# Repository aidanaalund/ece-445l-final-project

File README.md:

# ECE 445L Final Project

This final project is titled 'Magic Wand'. The user's hand is tracked with a sensor and the fans in the tubes will make a ping pong ball float to match the user's hand distance. Won professor's vote at the Spring 2025 Embedded Systems competition.

## 0 Repository Structure

The typical explanation for the repo structure. Lab specific instructions can be
found further below.

### 0.1 HW

The `hw` folder should contain your schematic and board files for your PCB or
circuits. In labs 1-5 and 10, you will be creating schematics for your circuit
in KiCad. 

### 0.2 SW

The `sw` folder should contain your application firmware and software written
for the lab. The `sw/inc` folder contains firmware drivers written for you by
Professor Valvano. Feel free to write your own (in fact, in some labs, you may
be required to write your own).

You can place any other source files in the `sw` folder. TAs will look at the
files you create and/or modify for software quality and for running your
project.

### 0.3 Resources

A couple files are provided in the Resources folder so you don't have to keep
searching for that one TI document. Some of them are immediately useful, like
the TM4C datasheet. Others may be useful for your final project, like the
TM4C_System_Design_Guidelines page.

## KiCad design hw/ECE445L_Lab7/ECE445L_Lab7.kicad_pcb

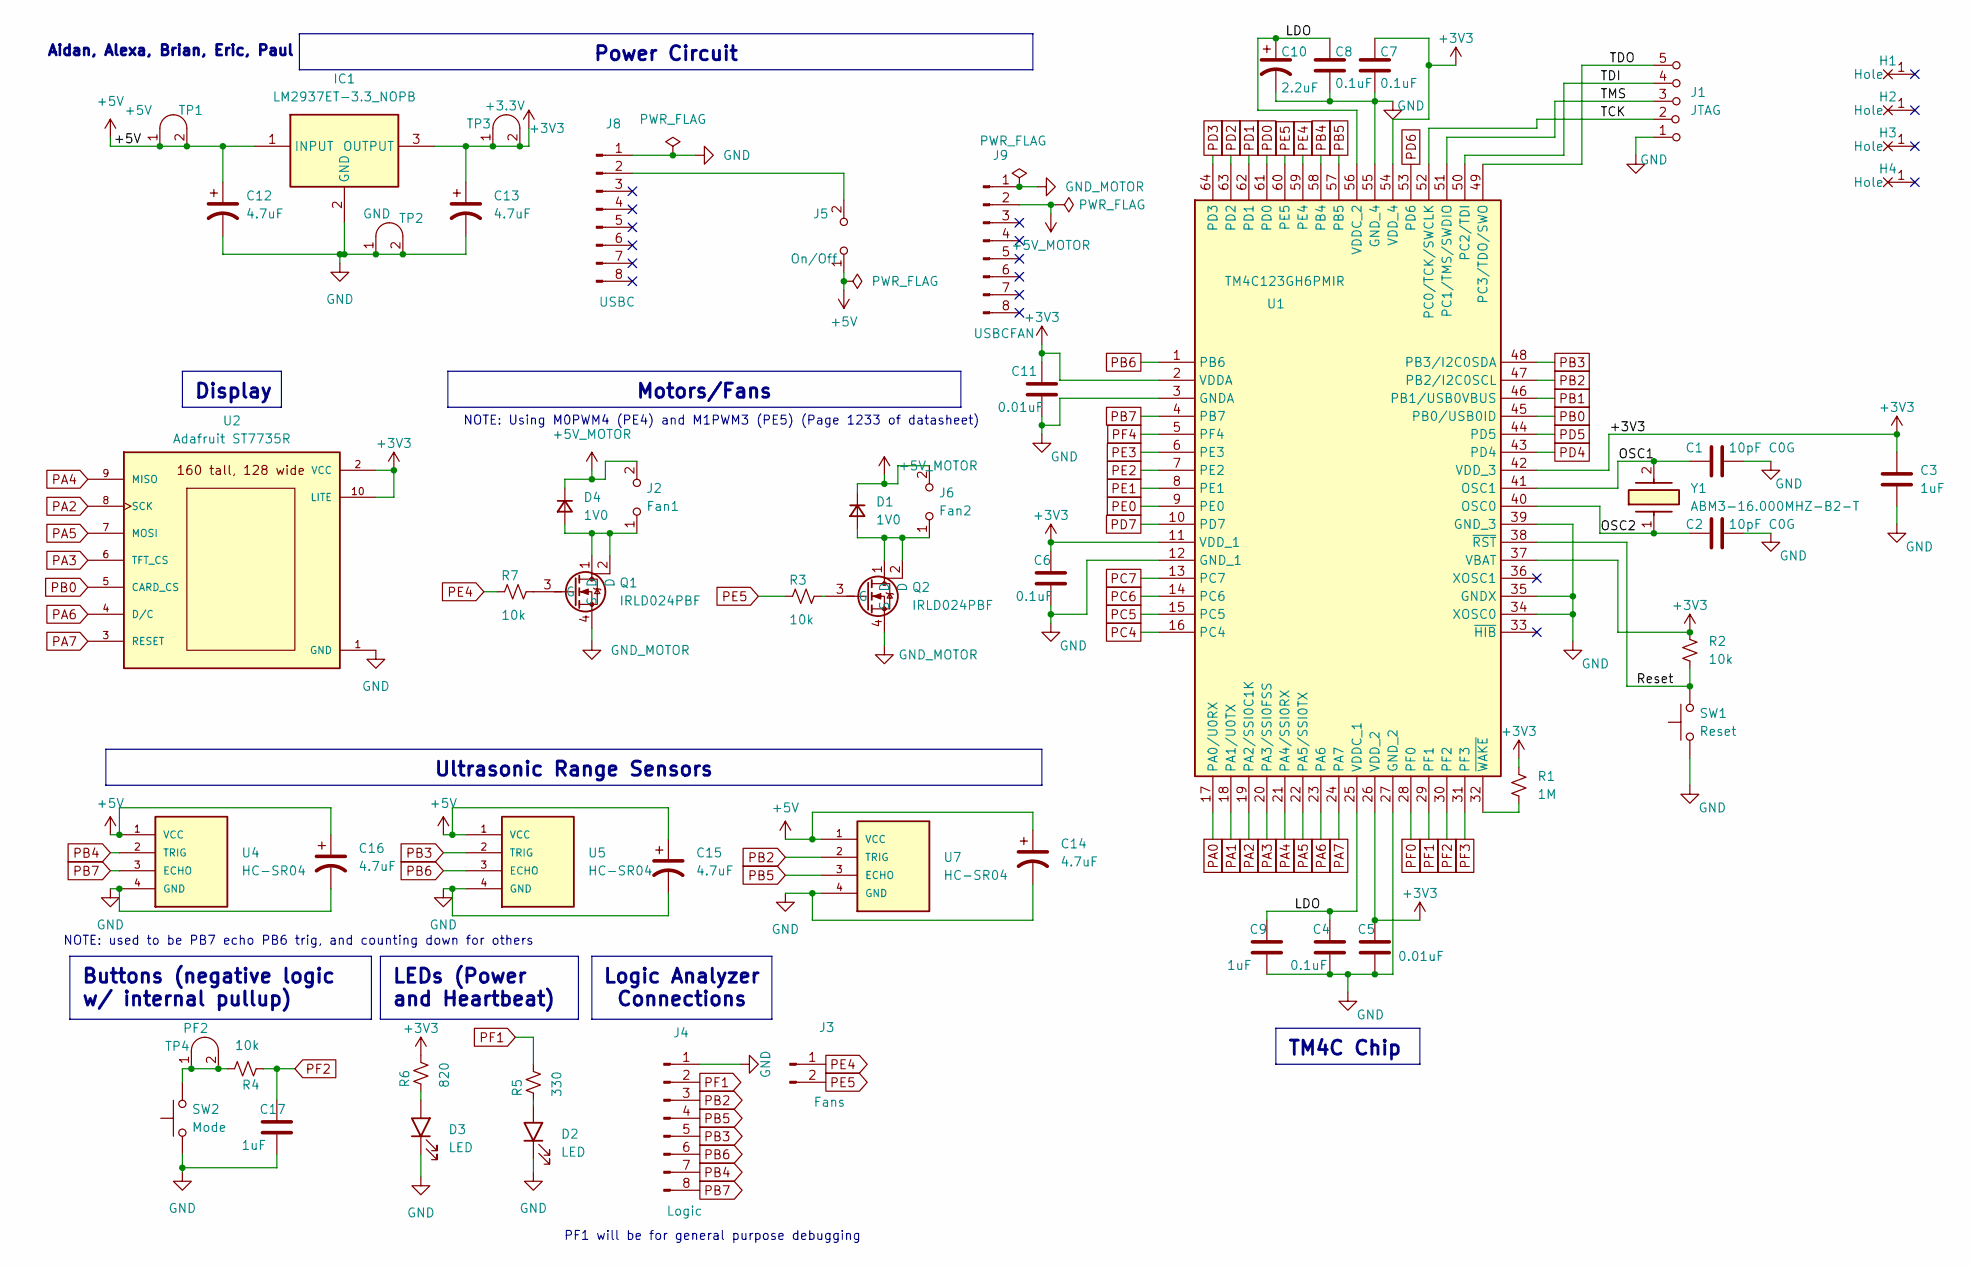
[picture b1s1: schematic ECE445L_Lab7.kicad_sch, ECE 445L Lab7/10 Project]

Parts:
C1, C2: 10pF C0G; C_Axial_200mil
C3, C9, C17: 1uF; C_Axial_200mil
C4, C6, C7, C8: 0.1uF; C_Axial_200mil
C5, C11: 0.01uF; C_Axial_200mil
C10: 2.2uF; CP_Radial_Tantal200mil
C12, C13, C14, C15, C16: 4.7uF; CP_Radial_Tantal200mil
D1, D4: 1V0; AFL-W2C8.9D
D2, D3: LED; LED_D5.0mm
H1, H2, H3, H4: MountingHole_4_40
IC1: LM2937ET-3.3_NOPB; TO254P470X1028X1955-3P; Mouser Part Number 926-LM2937ET-3.3NOPB
J1: JTAG; PinHeader_1x05_P2.54mm_Vertical
J2: Fan1; PinHeader_1x02_P2.54mm_Vertical
J3: Fans; PinHeader_1x02_P2.54mm_Vertical
J4: Logic; PinHeader_1x08_P2.54mm_Vertical
J5: On/Off; PinHeader_1x02_P2.54mm_Vertical
J6: Fan2; PinHeader_1x02_P2.54mm_Vertical
J8: USBC; PinHeader_1x08_P2.54mm_Vertical
J9: USBCFAN; PinHeader_1x08_P2.54mm_Vertical
Q1, Q2: IRLD024PBF; DIP920W60P254L490H457Q4N; Mouser Part Number 844-IRLD024PBF
R1: 1M; R_Axial_DIN0204_L3.6mm_D1.6mm_P7.62mm_Horizontal
R2, R3, R4, R7: 10k; R_Axial_DIN0204_L3.6mm_D1.6mm_P7.62mm_Horizontal
R5: 330; R_Axial_DIN0204_L3.6mm_D1.6mm_P7.62mm_Horizontal
R6: 820; R_Axial_DIN0204_L3.6mm_D1.6mm_P7.62mm_Horizontal
SW1: Reset; SW_PUSH_6mm
SW2: Mode; SW_PUSH_6mm
TP1: +5V; Testpoint_1x02_P2.54mm
TP2: GND; Testpoint_1x02_P2.54mm
TP3: +3.3V; Testpoint_1x02_P2.54mm
TP4: PF2; Testpoint_1x02_P2.54mm
U1: TM4C123GH6PMIR; QFP50P1200X1200X160-64N; Mouser Part Number 595-TM4C123GH6PMIR
U2: Adafruit ST7735R; adafruit_st7735r2
U4, U5, U7: HC-SR04; PinHeader_1x04_P2.54mm_Vertical
Y1: ABM3-16.000MHZ-B2-T; ABM3; Mouser Part Number 815-ABM3-16-B2-T

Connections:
+3V3: C3.1, C5.1, C6.1, C7.1, C11.1, C13.1, IC1.3 (OUTPUT), R1.1, R2.1, R6.2, TP3.1 (A), TP3.2 (B), U1.2 (VDDA), U1.11 (VDD_1), U1.26 (VDD_2), U1.37 (VBAT), U1.42 (VDD_3), U1.54 (VDD_4), U2.2 (VCC), U2.10 (LITE)
+5V: C12.1, C14.1, C15.1, C16.1, IC1.1 (INPUT), J5.1 (A), TP1.1 (A), TP1.2 (B), U4.1 (VCC), U5.1 (VCC), U7.1 (VCC)
+5V_MOTOR: D1.1 (K), D4.1 (K), J2.2 (B), J6.2 (B), J9.2
/LDO: C4.1, C8.1, C9.1, C10.1, U1.25 (VDDC_1), U1.56 (VDDC_2)
/OSC1: C1.1, U1.41 (OSC1), Y1.2
/OSC2: C2.1, U1.40 (OSC0), Y1.1
/Reset: R2.2, SW1.2, U1.38 (~RST)
/TCK: J1.2 (B), U1.52 (PC0/TCK/SWCLK)
/TDI: J1.4 (C), U1.50 (PC2/TDI)
/TDO: J1.5 (C), U1.49 (PC3/TDO/SWO)
/TMS: J1.3 (C), U1.51 (PC1/TMS/SWDIO)
GND: C1.2, C2.2, C3.2, C4.2, C5.2, C6.2, C7.2, C8.2, C9.2, C10.2, C11.2, C12.2, C13.2, C14.2, C15.2, C16.2, C17.2, D2.1 (K), D3.1 (K), IC1.2 (GND), J1.1 (A), J4.1, J8.1, SW1.1, SW2.1, TP2.1 (A), TP2.2 (B), U1.3 (GNDA), U1.12 (GND_1), U1.27 (GND_2), U1.34 (XOSC0), U1.35 (GNDX), U1.39 (GND_3), U1.55 (GND_4), U2.1 (GND), U4.4 (GND), U5.4 (GND), U7.4 (GND)
GND_MOTOR: J9.1, Q1.4 (S), Q2.4 (S)
unnamed: D1.2 (A), J6.1 (A), Q2.1 (D), Q2.2 (D)
unnamed: D2.2 (A), R5.1
unnamed: D3.2 (A), R6.1
unnamed: D4.2 (A), J2.1 (A), Q1.1 (D), Q1.2 (D)
unnamed: J5.2 (B), J8.2
unnamed: Q1.3 (G), R7.2
unnamed: Q2.3 (G), R3.2
unnamed: R4.2, SW2.2, TP4.1 (A), TP4.2 (B)
unnamed: R1.2, U1.32 (~WAKE)
PA0: U1.17 (PA0/U0RX)
PA1: U1.18 (PA1/U0TX)
PA2: U1.19 (PA2/SSI0C1K), U2.8 (SCK)
PA3: U1.20 (PA3/SSI0FSS), U2.6 (TFT_CS)
PA4: U1.21 (PA4/SSI0RX), U2.9 (MISO)
PA5: U1.22 (PA5/SSI0TX), U2.7 (MOSI)
PA6: U1.23 (PA6), U2.4 (D/C)
PA7: U1.24 (PA7), U2.3 (RESET)
PB0: U1.45 (PB0/USB0ID), U2.5 (CARD_CS)
PB1: U1.46 (PB1/USB0VBUS)
PB2: J4.3, U1.47 (PB2/I2C0SCL), U7.2 (TRIG)
PB3: J4.5, U1.48 (PB3/I2C0SDA), U5.2 (TRIG)
PB4: J4.7, U1.58 (PB4), U4.2 (TRIG)
PB5: J4.4, U1.57 (PB5), U7.3 (ECHO)
PB6: J4.6, U1.1 (PB6), U5.3 (ECHO)
PB7: J4.8, U1.4 (PB7), U4.3 (ECHO)
PC4: U1.16 (PC4)
PC5: U1.15 (PC5)
PC6: U1.14 (PC6)
PC7: U1.13 (PC7)
PD0: U1.61 (PD0)
PD1: U1.62 (PD1)
PD2: U1.63 (PD2)
PD3: U1.64 (PD3)
PD4: U1.43 (PD4)
PD5: U1.44 (PD5)
PD6: U1.53 (PD6)
PD7: U1.10 (PD7)
PE0: U1.9 (PE0)
PE1: U1.8 (PE1)
PE2: U1.7 (PE2)
PE3: U1.6 (PE3)
PE4: J3.1, R7.1, U1.59 (PE4)
PE5: J3.2, R3.1, U1.60 (PE5)
PF0: U1.28 (PF0)
PF1: J4.2, R5.2, U1.29 (PF1)
PF2: C17.1, R4.1, U1.30 (PF2)
PF3: U1.31 (PF3)
PF4: U1.5 (PF4)

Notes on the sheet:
Logic Analyzer Connections
Buttons (negative logic w/ internal pullup)
Motors/Fans
LEDs (Power and Heartbeat)
Ultrasonic Range Sensors
Display
Power Circuit
TM4C Chip
NOTE: used to be PB7 echo PB6 trig, and counting down for others
PF1 will be for general purpose debugging
Aidan, Alexa, Brian, Eric, Paul
NOTE: Using M0PWM4 (PE4) and M1PWM3 (PE5) (Page 1233 of datasheet)

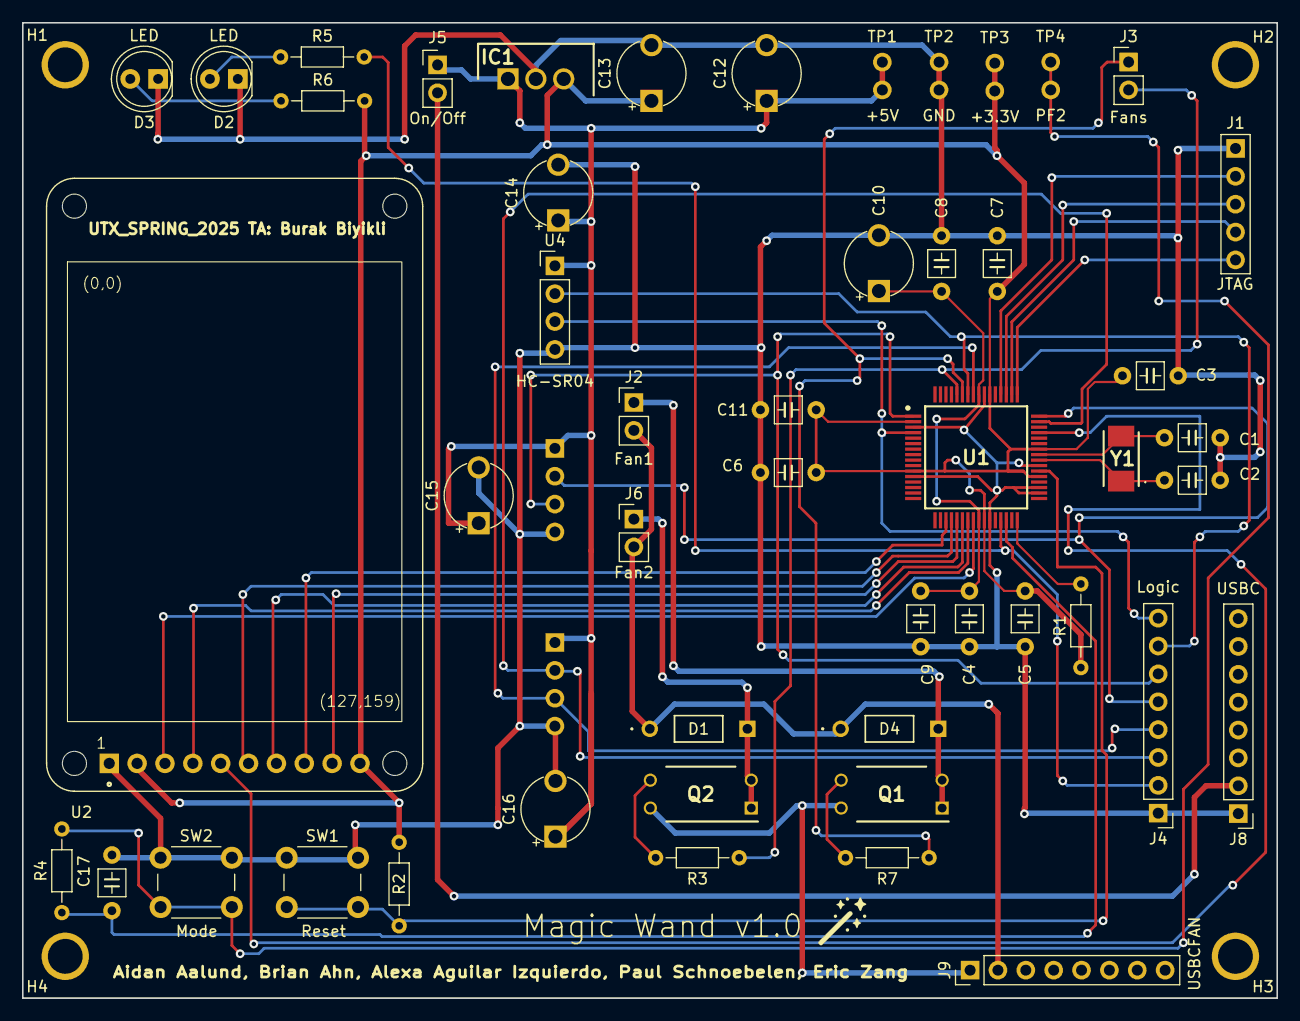
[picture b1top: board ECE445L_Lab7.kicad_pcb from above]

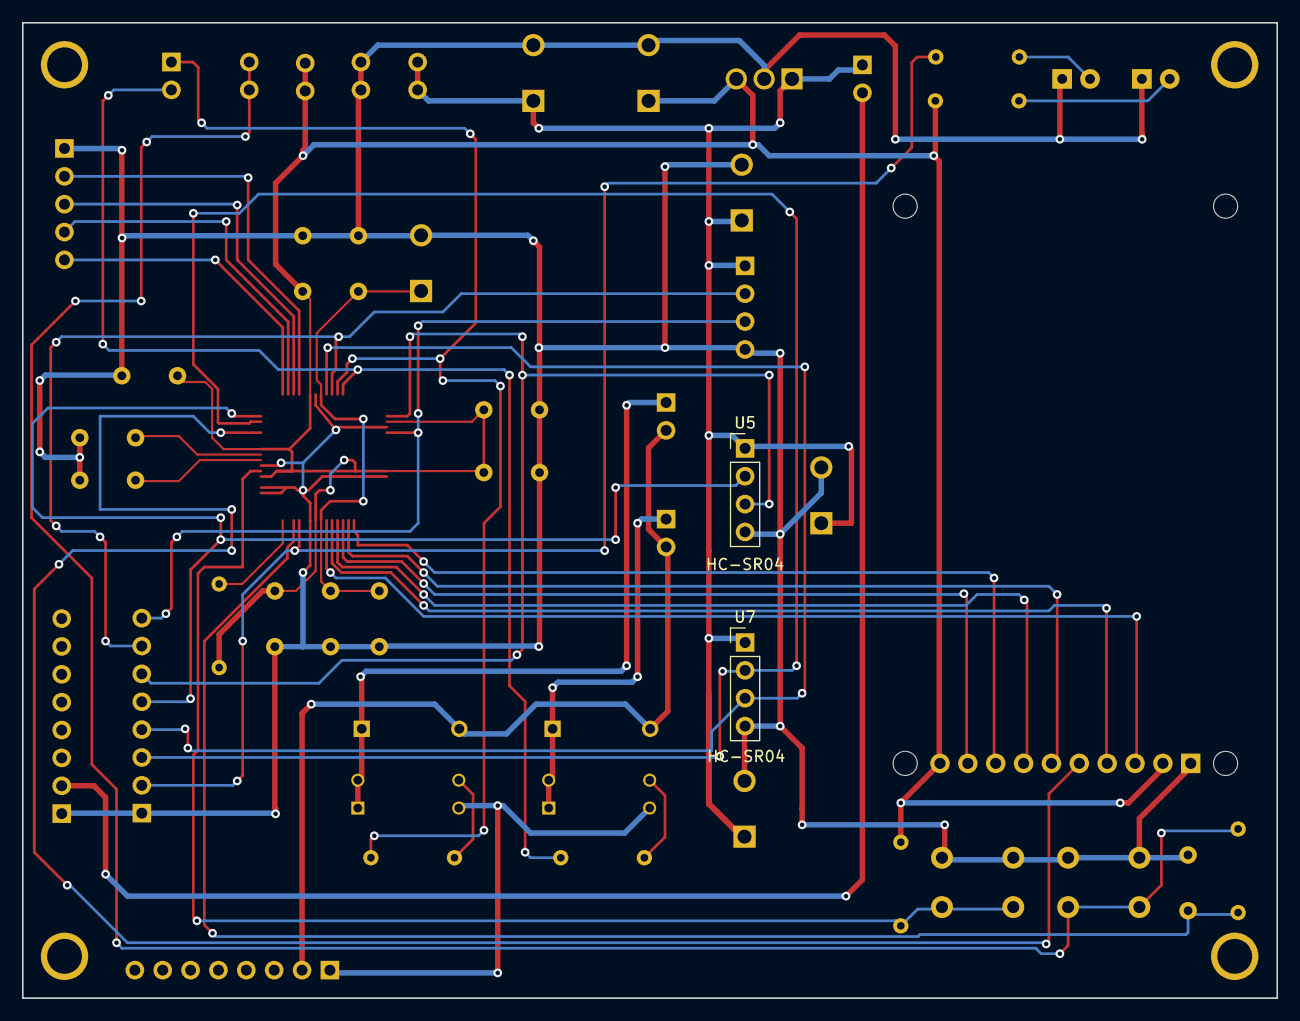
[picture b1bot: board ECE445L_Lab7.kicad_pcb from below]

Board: 2 copper layers, 114.4 x 88.9 mm, 55 parts (2 on the bottom side), 39 nets.

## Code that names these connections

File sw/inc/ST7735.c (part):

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// ST7735
// Backlight (pin 10) connected to +3.3 V
// MISO (pin 9) unconnected
// SCK (pin 8) connected to PA2 (SSI0Clk)
// MOSI (pin 7) connected to PA5 (SSI0Tx)
// TFT_CS (pin 6) connected to PA3 (SSI0Fss)
// CARD_CS (pin 5) unconnected
// Data/Command (pin 4) connected to PA6 (GPIO), high for data, low for command
// RESET (pin 3) connected to PA7 (GPIO)
// VCC (pin 2) connected to +3.3 V
// Gnd (pin 1) connected to ground

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// Silkscreen Label (SDC side up; LCD side down) - Connection
// VCC  - +3.3 V
// GND  - Ground
// !SCL - PA2 Sclk SPI clock from microcontroller to TFT or SDC
// !SDA - PA5 MOSI SPI data from microcontroller to TFT or SDC
// DC   - PA6 TFT data/command
// RES  - PA7 TFT reset
// CS   - PA3 TFT_CS, active low to enable TFT
// *CS  - (NC) SDC_CS, active low to enable SDC
// MISO - (NC) MISO SPI data from SDC to microcontroller
// SDA   (NC) I2C data for ADXL345 accelerometer
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// Silkscreen Label (SDC side up; LCD side down) - Connection
// VCC  - +3.3 V
// GND  - Ground
// !SCL - PA2 Sclk SPI clock from microcontroller to TFT or SDC
// !SDA - PA5 MOSI SPI data from microcontroller to TFT or SDC
// DC   - PA6 TFT data/command
// RES  - PA7 TFT reset
// CS   - PA3 TFT_CS, active low to enable TFT
// *CS  - (NC) SDC_CS, active low to enable SDC
// MISO - (NC) MISO SPI data from SDC to microcontroller
// X (NC) analog input X-axis from ADXL335 accelerometer
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// MOSI   (pin 13) SDC, MOSI
// MISO   (pin 12) SDC, MISO
// SCK    (pin 11) SDC, serial clock
// CS     (pin 10) TFT, PA3 (SSI0Fss)
// SCL    (pin 9)  TFT, SCK  PA2 (SSI0Clk)
// SDA    (pin 8)  TFT, MOSI PA5 (SSI0Tx)
// A0     (pin 7)  TFT, Data/Command PA6 (GPIO), high for data, low for command
// RESET  (pin 6)  TFT, to PA7 (GPIO)
// NC     (pins 3,4,5) not connected
// VCC    (pin 2)  connected to +3.3 V
// GND    (pin 1)  connected to ground
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// Tyenaza Tyenazaqhf72mi9s3
// ST7735
// LED (pin 8) connected to +3.3 V
// SCK (pin 7) connected to PA2 (SSI0Clk)
// SDA (pin 6) MOSI, connected to PA5 (SSI0Tx)
// A0  (pin 5) Data/Command connected to PA6 (GPIO), high for data, low for command
// RESET (pin 4) connected to PA7 (GPIO)
// CS  (pin 3) connected to PA3 (SSI0Fss)
// Gnd (pin 2) connected to ground
// VCC (pin 1) connected to +3.3 V

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
  // toggle RST low to reset; CS low so it'll listen to us
  // SSI0Fss is temporarily used as GPIO
  GPIO_PORTA_DIR_R |= 0xC8;             // make PA3,6,7 out
  GPIO_PORTA_AFSEL_R &= ~0xC8;          // disable alt funct on PA3,6,7
  GPIO_PORTA_DEN_R |= 0xC8;             // enable digital I/O on PA3,6,7
                                        // configure PA3,6,7 as GPIO
  GPIO_PORTA_PCTL_R = (GPIO_PORTA_PCTL_R&0x00FF0FFF)+0x00000000;
  GPIO_PORTA_AMSEL_R &= ~0xC8;          // disable analog functionality on PA3,6,7
  TFT_CS = TFT_CS_LOW;
  RESET = RESET_HIGH;
  Delay1ms(500);
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  Delay1ms(500);

  // initialize SSI0
  GPIO_PORTA_AFSEL_R |= 0x2C;           // enable alt funct on PA2,3,5
  GPIO_PORTA_DEN_R |= 0x2C;             // enable digital I/O on PA2,3,5
                                        // configure PA2,3,5 as SSI
  GPIO_PORTA_PCTL_R = (GPIO_PORTA_PCTL_R&0xFF0F00FF)+0x00202200;
  GPIO_PORTA_AMSEL_R &= ~0x2C;          // disable analog functionality on PA2,3,5
  SSI0_CR1_R &= ~SSI_CR1_SSE;           // disable SSI
  SSI0_CR1_R &= ~SSI_CR1_MS;            // master mode
                                        // configure for system clock/PLL baud clock source
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
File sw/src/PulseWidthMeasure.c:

// PulseWidthMeasure.c
// Runs on LM4F120/TM4C123
// Use Timer0A in 24-bit edge time mode to request interrupts on the falling
// edge of PB6 (T0CCP0). 
// Use Timer0B in 24-bit edge time mode rising edge of PB7(T0CCP1) is latched, and 
// the system measures pulse between pulses.
// Daniel Valvano
// April 2, 2018

/* This example accompanies the book
   "Embedded Systems: Real Time Interfacing to Arm Cortex M Microcontrollers",
   ISBN: 978-1463590154, Jonathan Valvano, copyright (c) 2018
   Example 6.5, Program 6.5

 Copyright 2018 by Jonathan W. Valvano, valvano@mail.utexas.edu
    You may use, edit, run or distribute this file
    as long as the above copyright notice remains
 THIS SOFTWARE IS PROVIDED "AS IS".  NO WARRANTIES, WHETHER EXPRESS, IMPLIED
 OR STATUTORY, INCLUDING, BUT NOT LIMITED TO, IMPLIED WARRANTIES OF
 MERCHANTABILITY AND FITNESS FOR A PARTICULAR PURPOSE APPLY TO THIS SOFTWARE.
 VALVANO SHALL NOT, IN ANY CIRCUMSTANCES, BE LIABLE FOR SPECIAL, INCIDENTAL,
 OR CONSEQUENTIAL DAMAGES, FOR ANY REASON WHATSOEVER.
 For more information about my classes, my research, and my books, see
 http://users.ece.utexas.edu/~valvano/
 */


#include <stdint.h>
#include "PulseWidthMeasure.h"
#include "Motor.h"
#include "../inc/Timer0A.h"
#include "../inc/Timer2A.h" // USE THESE TWO WHEN YOU INTEGRATE
#include "../inc/Timer3A.h" // ................................
#include "../inc/tm4c123gh6pm.h"
#include "../inc/PLL.h"
#include "../inc/CortexM.h"
#include "../inc/LaunchPad.h"

uint32_t startTimeTubeOne = 0;
uint32_t startTimeTubeTwo = 0;
uint32_t startTimeTubeThree = 0;

volatile uint32_t distanceOne = 0;
volatile uint32_t distanceTwo = 0;
volatile uint32_t distanceThree = 0;

volatile uint32_t Count = 0;
volatile uint32_t Count2 = 0;

uint32_t firstClock = 0;

int tubeDoneOne = 0;                   // set each falling
int tubeDoneTwo = 0;
int tubeDoneThree = 0;

//void timeInMicro (void) {
//	Count += 1;
//}

void Timer2PWMMeasure_Init(void) {
    // Enable the clock for Timer 2
    SYSCTL_RCGCTIMER_R |= SYSCTL_RCGCTIMER_R2;  
    while ((SYSCTL_PRTIMER_R & SYSCTL_PRTIMER_R2) == 0);  // Wait for Timer 2 to be ready

    // Disable Timer 2 before configuration
    TIMER2_CTL_R = 0;

    // Configure Timer 2 as a 32-bit timer
    TIMER2_CFG_R = TIMER_CFG_32_BIT_TIMER;

    // Set Timer 2 to periodic mode
    TIMER2_TAMR_R = TIMER_TAMR_TAMR_PERIOD;  // Periodic mode

    // Set the direction to count up (clear TACDIR for up-counting)
    TIMER2_TAMR_R &= ~TIMER_TAMR_TACDIR;  // Clear the TACDIR bit to make it count up

    // Set the maximum value for the timer (maximum 32-bit value)
    TIMER2_TAILR_R = 0xFFFFFFFF;  // Set to maximum 32-bit value (up to 4,294,967,295)

    // Enable Timer 2A
    TIMER2_CTL_R |= TIMER_CTL_TAEN;
}

void GPIOPortB_Handler(void){
	
	if (GPIO_PORTB_RIS_R & 0x80) {// pb7
		GPIO_PORTB_ICR_R = 0x80;
		if (tubeDoneOne == 0) {
			tubeDoneOne = 1;
			startTimeTubeOne = TIMER2_TAR_R;
			GPIO_PORTB_DATA_R |= 0x02;
		} else if (tubeDoneOne == 1) {
			GPIO_PORTB_DATA_R &= ~0x02;
			if (TIMER2_TAR_R < startTimeTubeOne) { 
				uint32_t test = TIMER2_TAR_R;
				distanceOne = startTimeTubeOne - TIMER2_TAR_R; /// 29; // Fixed point (units of 0.5cm) (moved to display.c)
			} else {
				uint32_t test = TIMER2_TAR_R;
				distanceOne = (startTimeTubeOne + 0xFFFFFFFF)- TIMER2_TAR_R ; // MIGHT NEED TO MAKE THIS VOLATILE
			}
			//if(distanceOne > 100){distanceOne = 0;} // 50cm cap
			tubeDoneOne = 0;
		}

	}
	
	if (GPIO_PORTB_RIS_R & 0x40) {// pb6
		GPIO_PORTB_ICR_R = 0x40;
		uint32_t test = TIMER2_TAR_R;
		if (tubeDoneTwo == 0) {
			tubeDoneTwo = 1;
			startTimeTubeTwo = TIMER2_TAR_R;
		} else if (tubeDoneTwo == 1) {
			if (TIMER2_TAR_R < startTimeTubeTwo) { 
				distanceTwo =  startTimeTubeTwo - TIMER2_TAR_R; /// 29; // Fixed point (units of 0.5cm) (moved to display.c)
			} else {
				distanceTwo = (startTimeTubeTwo + 0xFFFFFFFF)- TIMER2_TAR_R; // MIGHT NEED TO MAKE THIS VOLATILE
			}
			tubeDoneTwo = 0;
		}

	}
	
	if (GPIO_PORTB_RIS_R & 0x20) {// pb5
		GPIO_PORTB_ICR_R = 0x20;
		if (tubeDoneThree == 0) {
			tubeDoneThree = 1;
			startTimeTubeThree = TIMER2_TAR_R;
		} else if (tubeDoneThree == 1) {
			if (TIMER2_TAR_R < startTimeTubeThree) { 
				distanceThree = startTimeTubeThree - TIMER2_TAR_R; /// 29; // Fixed point (units of 0.5cm) (moved to display.c)
			} else {
				distanceThree = (startTimeTubeThree + 0xFFFFFFFF)- TIMER2_TAR_R; // MIGHT NEED TO MAKE THIS VOLATILE
			}
			tubeDoneThree = 0;
		}
		
	}
	
	//if (((tubeDoneOne == 1) || (tubeDoneTwo == 1) || (tubeDoneThree == 1)) && (firstClock == 0)) {
	//	firstClock = 1;
	//	Count = 0;
	//	Timer2A_Init(timeInMicro, 80, 7);
	//} 
	
	//if ((tubeDoneOne == 0) && (tubeDoneTwo == 0) && (tubeDoneThree == 0)){  // Added firstClock == 1
	//	Timer2A_Stop();
	//	firstClock = 0;
	//	Count = 0;
	//}	
}


void SendPulse(void) {
	if (Count2 == 6000) { // 60ms
		GPIO_PORTB_DATA_R |= 0x1C;
		Count2 = 0;
	} else {
		GPIO_PORTB_DATA_R &= ~0x1C;
	}
	Count2++;
}

void PWMeasure2_Init(void){ // TM4C123 code
  //SYSCTL_RCGCTIMER_R |= 0x01;      // activate timer0
  SYSCTL_RCGCGPIO_R |= 0x02;       // activate port B
	while ((SYSCTL_PRGPIO_R & 0x02) == 0) {}
  tubeDoneOne = 0;                        // allow time to finish activating
	tubeDoneTwo = 0;
	tubeDoneThree = 0;
	
  GPIO_PORTB_DIR_R &= ~0xE0;       // make PB5, PB6, PB7 inputs
  GPIO_PORTB_DEN_R |= 0xE0;        // enable digital PB7
  //GPIO_PORTB_AFSEL_R |= 0xE0;      // enable alt funct on PB7 #Not sure if necessary
	GPIO_PORTB_AFSEL_R &= ~0xE0;		//No alternate function
	GPIO_PORTB_IS_R &= ~0xE0; // make only detect edges
  GPIO_PORTB_IBE_R |= 0xE0; // Detect both edges
  //GPIO_PORTB_PCTL_R = (GPIO_PORTB_PCTL_R&0x00FFFFFF)+0x77000000; //Also not sure if necessary, only for alternate functions on PB6 and 7
	GPIO_PORTB_ICR_R = 0xE0; // clear interrupt flag
  GPIO_PORTB_IM_R |= 0xE0; // enable interrupts
	NVIC_PRI0_R = (NVIC_PRI0_R & 0xFFFFFF00) | 0x00000020;
	//NVIC_PRI0_R = (NVIC_PRI0_R & 0xFF1FFFFF) | (1 << 5);
  NVIC_EN0_R |= (1 << 1); // enable port b interrupt
	
  //TIMER0_CTL_R &= ~0x00000001;     // disable timers 0A and 0B
  //TIMER0_CFG_R = 0x00000004;       // configure for 16-bit timer mode
  // **** timer0A initialization ****
  //TIMER0_TAMR_R = 0x00000007;
  //TIMER0_CTL_R = (TIMER0_CTL_R&(~0x0C))+0x04; // falling edge TODO: should be rising
	//TIMER0_CTL_R = (TIMER0_CTL_R&(~0x0C))+0x00; //Rising
  //TIMER0_TAILR_R = 0x0000FFFF;     // start value
  //TIMER0_TAPR_R = 0xFF;            // activate prescale, creating 24-bit 
  //TIMER0_IMR_R |= 0x00000004;      // enable capture match interrupt
  //TIMER0_ICR_R = 0x00000004;       // clear timer0A capture match flag
  // **** timer0B initialization ****
//  TIMER0_TBMR_R = 0x00000007;
//  TIMER0_CTL_R = (TIMER0_CTL_R&(~0x0C00))+0x00; // rising edge TODO: should be falling
//  TIMER0_TBILR_R = 0x0000FFFF;     // start value
//  TIMER0_TBPR_R = 0xFF;            // activate prescale, creating 24-bit 
//  TIMER0_IMR_R &= ~0x0700;         // disable all interrupts for timer0B
	
  //TIMER0_CTL_R |= 0x00000001;      // enable timers 0A
  // **** interrupt initialization ****
	SYSCTL_RCGCGPIO_R |= 0x02; // enable clock for Port B
	while ((SYSCTL_PRGPIO_R & 0x02) == 0) {}
	GPIO_PORTB_DIR_R |= 0x1E; // set pb2,3,4 as output (connect to speaker)
	GPIO_PORTB_DEN_R |= 0x1E; // enable digital I/O on pb2,3,4
		
	Timer3A_Init(&SendPulse, 800, 7); // -> set this to PWM pin?
}

uint32_t GetDesiredPosition() {
	return distanceOne;
}

uint32_t GetLeftPosition() {
	return distanceTwo;
}

uint32_t GetRightPosition() {
	return distanceThree;
}

void SensorSetup() {
	Timer2PWMMeasure_Init();
	PWMeasure2_Init();      // initialize 24-bit timer0A in capture mode
}


//debug code
int mainDistance(void){           
  PLL_Init(Bus80MHz);     // 80 MHz clock
  LaunchPad_Init();       // activate port F
	SensorSetup();
	
  EnableInterrupts();
  while(1){
    WaitForInterrupt();
  }
}

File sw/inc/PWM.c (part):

// PWM.c
// Runs on TM4C123
// Use PWM0A/PB6 and PWM0B/PB7 to generate pulse-width modulated outputs.
// Daniel Valvano
// March 28, 2014

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

// period is 16-bit number of PWM clock cycles in one period (3<=period)
// period for PB6 and PB7 must be the same
// duty is number of PWM clock cycles output is high  (2<=duty<=period-1)
// PWM clock rate = processor clock rate/SYSCTL_RCC_PWMDIV
//                = BusClock/2
//                = 80 MHz/2 = 40 MHz (in this example)
// Output on PB6/M0PWM0
void PWM0A_Init(uint16_t period, uint16_t duty){
  SYSCTL_RCGCPWM_R |= 0x01;             // 1) activate PWM0
  SYSCTL_RCGCGPIO_R |= 0x02;            // 2) activate port B
  while((SYSCTL_PRGPIO_R&0x02) == 0){};
  GPIO_PORTB_AFSEL_R |= 0x40;           // enable alt funct on PB6
  GPIO_PORTB_PCTL_R &= ~0x0F000000;     // configure PB6 as PWM0
  GPIO_PORTB_PCTL_R |= 0x04000000;
  GPIO_PORTB_AMSEL_R &= ~0x40;          // disable analog functionality on PB6
  GPIO_PORTB_DEN_R |= 0x40;             // enable digital I/O on PB6
  SYSCTL_RCC_R = 0x00100000 |           // 3) use PWM divider
      (SYSCTL_RCC_R & (~0x000E0000));   //    configure for /2 divider
  PWM0_0_CTL_R = 0;                     // 4) re-loading down-counting mode
  PWM0_0_GENA_R = 0xC8;                 // low on LOAD, high on CMPA down
  // PB6 goes low on LOAD
  // PB6 goes high on CMPA down
  PWM0_0_LOAD_R = period - 1;           // 5) cycles needed to count down to 0
  PWM0_0_CMPA_R = duty - 1;             // 6) count value when output rises
  PWM0_0_CTL_R |= 0x00000001;           // 7) start PWM0
  PWM0_ENABLE_R |= 0x00000001;          // enable PB6/M0PWM0
}
// change duty cycle of PB6
// duty is number of PWM clock cycles output is high  (2<=duty<=period-1)
void PWM0A_Duty(uint16_t duty){
  PWM0_0_CMPA_R = duty - 1;             // 6) count value when output rises
}
// period is 16-bit number of PWM clock cycles in one period (3<=period)
// period for PB6 and PB7 must be the same
// duty is number of PWM clock cycles output is high  (2<=duty<=period-1)
// PWM clock rate = processor clock rate/SYSCTL_RCC_PWMDIV
//                = BusClock/2
//                = 80 MHz/2 = 40 MHz (in this example)
// Output on PB7/M0PWM1
void PWM0B_Init(uint16_t period, uint16_t duty){
  volatile unsigned long delay;
  SYSCTL_RCGCPWM_R |= 0x01;             // 1) activate PWM0
  SYSCTL_RCGCGPIO_R |= 0x02;            // 2) activate port B
  delay = SYSCTL_RCGCGPIO_R;            // allow time to finish activating
  GPIO_PORTB_AFSEL_R |= 0x80;           // enable alt funct on PB7
  GPIO_PORTB_PCTL_R &= ~0xF0000000;     // configure PB7 as M0PWM1
  GPIO_PORTB_PCTL_R |= 0x40000000;
  GPIO_PORTB_AMSEL_R &= ~0x80;          // disable analog functionality on PB7
  GPIO_PORTB_DEN_R |= 0x80;             // enable digital I/O on PB7
  SYSCTL_RCC_R |= SYSCTL_RCC_USEPWMDIV; // 3) use PWM divider
  SYSCTL_RCC_R &= ~SYSCTL_RCC_PWMDIV_M; //    clear PWM divider field
  SYSCTL_RCC_R += SYSCTL_RCC_PWMDIV_2;  //    configure for /2 divider
  PWM0_0_CTL_R = 0;                     // 4) re-loading down-counting mode
  PWM0_0_GENB_R = (PWM_0_GENB_ACTCMPBD_ONE|PWM_0_GENB_ACTLOAD_ZERO);
  // PB7 goes low on LOAD
  // PB7 goes high on CMPB down
  PWM0_0_LOAD_R = period - 1;           // 5) cycles needed to count down to 0
  PWM0_0_CMPB_R = duty - 1;             // 6) count value when output rises
  PWM0_0_CTL_R |= 0x00000001;           // 7) start PWM0
  PWM0_ENABLE_R |= 0x00000002;          // enable PB7/M0PWM1
}
// change duty cycle of PB7
// duty is number of PWM clock cycles output is high  (2<=duty<=period-1)
void PWM0B_Duty(uint16_t duty){
  PWM0_0_CMPB_R = duty - 1;             // 6) count value when output rises
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      (SYSCTL_RCC_R & (~0x000E0000));   //    configure for /2 divider
  PWM0_3_CTL_R = 0;                     // 4) re-loading down-counting mode
  PWM0_3_GENA_R = 0xC8;                 // low on LOAD, high on CMPA down
  // PB6 goes low on LOAD
  // PB6 goes high on CMPA down
  PWM0_3_LOAD_R = period - 1;           // 5) cycles needed to count down to 0
  PWM0_3_CMPA_R = duty - 1;             // 6) count value when output rises
  PWM0_3_CTL_R |= 0x00000001;           // 7) start PWM0
  PWM0_ENABLE_R |= 0x00000040;          // enable PD0/M0PWM6
}
// change duty cycle of PB6
// duty is number of PWM clock cycles output is high  (2<=duty<=period-1)
void PWM0G_Duty(uint16_t duty){
  PWM0_3_CMPA_R = duty - 1;             // 6) count value when output rises
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// PWM clock rate = processor clock rate/SYSCTL_RCC_PWMDIV
//                = BusClock/2
//                = 80 MHz/2 = 40 MHz (in this example)
// Output on PE4/M0PWM4
void PWM0E_Init(uint32_t period, uint32_t duty){
  SYSCTL_RCGCPWM_R |= 0x01;             // 1) activate PWM0
  SYSCTL_RCGCGPIO_R |= 0x10;            // 2) activate port E
  while((SYSCTL_PRGPIO_R&0x10) == 0){}; // wait for port E to be ready
  GPIO_PORTE_AFSEL_R |= 0x10;           // enable alt funct on PE4
  GPIO_PORTE_PCTL_R &= ~0x000F0000;     // configure PE4 as PWM4
  GPIO_PORTE_PCTL_R |= 0x00040000;      // 4 specifies M0PWM4 function
  GPIO_PORTE_AMSEL_R &= ~0x10;          // disable analog functionality on PE4
  GPIO_PORTE_DEN_R |= 0x10;             // enable digital I/O on PE4
  SYSCTL_RCC_R = 0x00100000 |           // 3) use PWM divider
      (SYSCTL_RCC_R & (~0x000E0000));   //    configure for /2 divider
  PWM0_2_CTL_R = 0;                     // 4) re-loading down-counting mode
  PWM0_2_GENA_R = 0xC8;                 // low on LOAD, high on CMPA down
  // PE4 goes low on LOAD
  // PE4 goes high on CMPA down
  PWM0_2_LOAD_R = period - 1;           // 5) cycles needed to count down to 0
  PWM0_2_CMPA_R = duty - 1;             // 6) count value when output rises
  PWM0_2_CTL_R |= 0x00000001;           // 7) start PWM0
  PWM0_ENABLE_R |= 0x00000010;          // enable PE4/M0PWM4
}

// change duty cycle of PE4
// duty is number of PWM clock cycles output is high  (2<=duty<=period-1)
void PWM0E_Duty(uint16_t duty){
  PWM0_2_CMPA_R = duty - 1;             // count value when output rises
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// PWM clock rate = processor clock rate/SYSCTL_RCC_PWMDIV
//                = BusClock/2
//                = 80 MHz/2 = 40 MHz (in this example)
// Output on PE5/M1PWM3
void PWM1F_Init(uint16_t period, uint16_t duty){
  SYSCTL_RCGCPWM_R |= 0x02;             // 1) activate PWM1
  SYSCTL_RCGCGPIO_R |= 0x10;            // 2) activate port E
  while((SYSCTL_PRGPIO_R&0x10) == 0){}; // wait for port E to be ready
  GPIO_PORTE_AFSEL_R |= 0x20;           // enable alt funct on PE5
  GPIO_PORTE_PCTL_R &= ~0x00F00000;     // configure PE5 as M1PWM3
  GPIO_PORTE_PCTL_R |= 0x00500000;      // 5 specifies M1PWM3 function
  GPIO_PORTE_AMSEL_R &= ~0x20;          // disable analog functionality on PE5
  GPIO_PORTE_DEN_R |= 0x20;             // enable digital I/O on PE5
  
  SYSCTL_RCC_R |= SYSCTL_RCC_USEPWMDIV; // 3) use PWM divider
  SYSCTL_RCC_R &= ~SYSCTL_RCC_PWMDIV_M; //    clear PWM divider field
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  
  PWM1_1_CTL_R = 0;                     // 4) re-loading down-counting mode
  PWM1_1_GENB_R = 0xC8;                 // low on LOAD, high on CMPB down
  // PE5 goes low on LOAD
  // PE5 goes high on CMPB down
  PWM1_1_LOAD_R = period - 1;           // 5) cycles needed to count down to 0
  PWM1_1_CMPB_R = duty - 1;             // 6) count value when output rises
  PWM1_1_CTL_R |= 0x00000001;           // 7) start PWM1 generator 1
  PWM1_ENABLE_R |= 0x00000008;          // enable PE5/M1PWM3
}

// change duty cycle of PE5/M1PWM3
// duty is number of PWM clock cycles output is high  (2<=duty<=period-1)
void PWM1F_Duty(uint16_t duty){
  PWM1_1_CMPB_R = duty - 1;             // count value when output rises
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// PWM clock rate = processor clock rate/SYSCTL_RCC_PWMDIV
//                = BusClock/2
//                = 80 MHz/2 = 40 MHz (in this example)
// Output on PE5/M0PWM5
void PWM0F_Init(uint32_t period, uint32_t duty){
  SYSCTL_RCGCPWM_R |= 0x01;             // 1) activate PWM0
  SYSCTL_RCGCGPIO_R |= 0x10;            // 2) activate port E
  while((SYSCTL_PRGPIO_R&0x10) == 0){}; // wait for port E to be ready
  GPIO_PORTE_AFSEL_R |= 0x20;           // enable alt funct on PE5
  GPIO_PORTE_PCTL_R &= ~0x00F00000;     // configure PE5 as M0PWM5
  GPIO_PORTE_PCTL_R |= 0x00400000;      // 4 specifies M0PWM5 function
  GPIO_PORTE_AMSEL_R &= ~0x20;          // disable analog functionality on PE5
  GPIO_PORTE_DEN_R |= 0x20;             // enable digital I/O on PE5
  
  SYSCTL_RCC_R |= SYSCTL_RCC_USEPWMDIV; // 3) use PWM divider
  SYSCTL_RCC_R &= ~SYSCTL_RCC_PWMDIV_M; //    clear PWM divider field
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  
  PWM0_2_CTL_R = 0;                     // 4) re-loading down-counting mode
  PWM0_2_GENB_R = (PWM_0_GENB_ACTCMPBD_ONE|PWM_0_GENB_ACTLOAD_ZERO);
  // PE5 goes low on LOAD
  // PE5 goes high on CMPB down
  PWM0_2_LOAD_R = period - 1;           // 5) cycles needed to count down to 0
  PWM0_2_CMPB_R = duty - 1;             // 6) count value when output rises
  PWM0_2_CTL_R |= 0x00000001;           // 7) start PWM0 generator 2
  PWM0_ENABLE_R |= 0x00000020;          // enable PE5/M0PWM5
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
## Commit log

2025-10-25 Added source files
2025-10-25 Added images from showcase
2025-10-25 Rename IMG_0046.JPEG to Showcase.JPEG
2025-10-25 Improved README for readability
2026-04-30 Removed .gcode files

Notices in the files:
sw/inc/PWM.c:
ISBN: 978-1463590154, Jonathan Valvano, copyright (c) 2015
"Embedded Systems: Real-Time Operating Systems for ARM Cortex M Microcontrollers",
ISBN: 978-1466468863, Jonathan Valvano, copyright (c) 2015
Copyright 2015 by Jonathan W. Valvano, valvano@mail.utexas.edu
sw/inc/ST7735.c:
MIT license, all text above must be included in any redistribution
"Embedded Systems: Introduction to ARM Cortex M Microcontrollers",
ISBN: 978-1469998749, Jonathan Valvano, copyright (c) 2020
ISBN: 978-1463590154, Jonathan Valvano, copyright (c) 2024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
